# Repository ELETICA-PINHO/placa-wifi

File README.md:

# placa-wifi
projeto placa-wifi versão 1.0

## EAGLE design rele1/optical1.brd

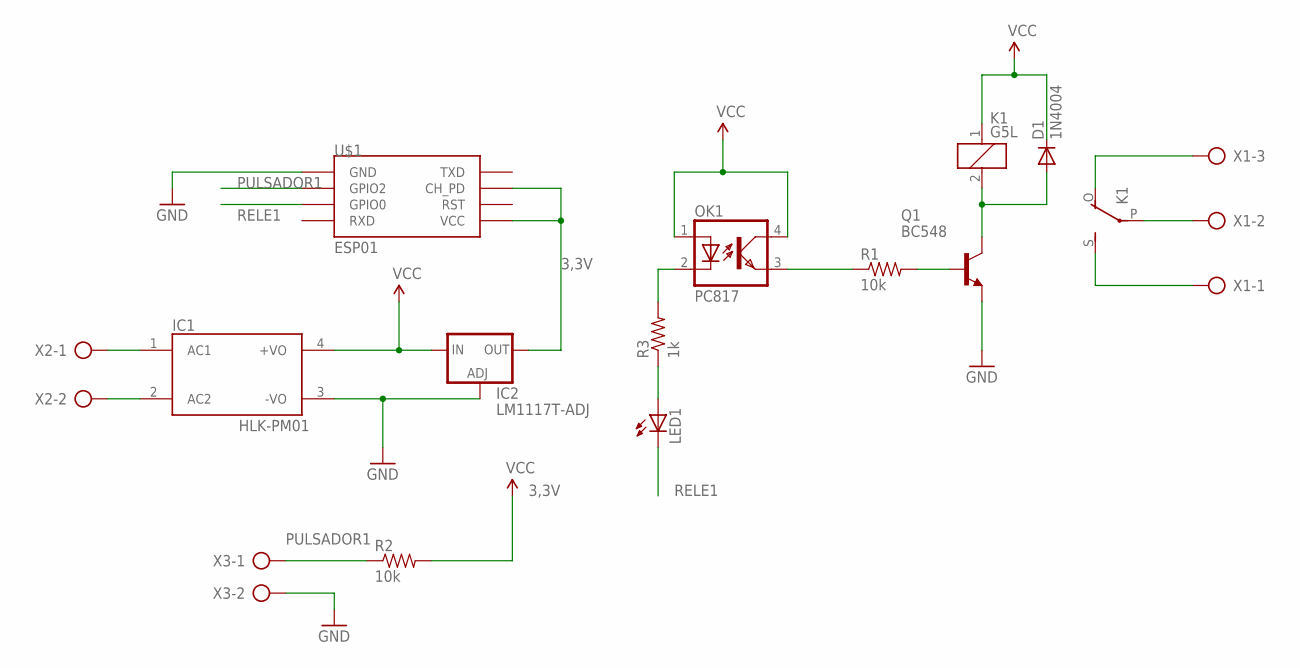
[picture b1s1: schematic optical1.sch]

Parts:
D1: 1N4004; DO41-10
IC1: HLK-PM01; HLK-PM**
IC2: LM1117T-ADJ; TO220
K1: G5L; G5LE
LED1: LED5MM
OK1: PC817; DIL04
Q1: BC548; TO92-EBC
R1, R2: 10k; AXIAL-0.3
R3: 1k; AXIAL-0.3
U$1: ESP01
X1: AK500/3-H
X2, X3: AK500/2-H

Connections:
3,3V: IC2.2 (OUT), R2.P$2 (2), U$1.CH_PD, U$1.VCC
GND: IC1.3 (-VO), IC2.1 (ADJ), Q1.E, U$1.GND, X3.2
unnamed: D1.A, K1.2, Q1.C
unnamed: K1.P, X1.2
unnamed: K1.S, X1.1
unnamed: K1.O, X1.3
unnamed: OK1.3 (EMIT), R1.P$1 (1)
unnamed: Q1.B, R1.P$2 (2)
unnamed: IC1.1 (AC1), X2.1
unnamed: IC1.2 (AC2), X2.2
unnamed: OK1.2 (C), R3.P$2 (2)
unnamed: LED1.A, R3.P$1 (1)
PULSADOR1: R2.P$1 (1), U$1.GPIO2, X3.1
RELE1: LED1.K (C), U$1.GPIO0
VCC: D1.C, IC1.4 (+VO), IC2.3 (IN), K1.1, OK1.1 (A), OK1.4 (COL)

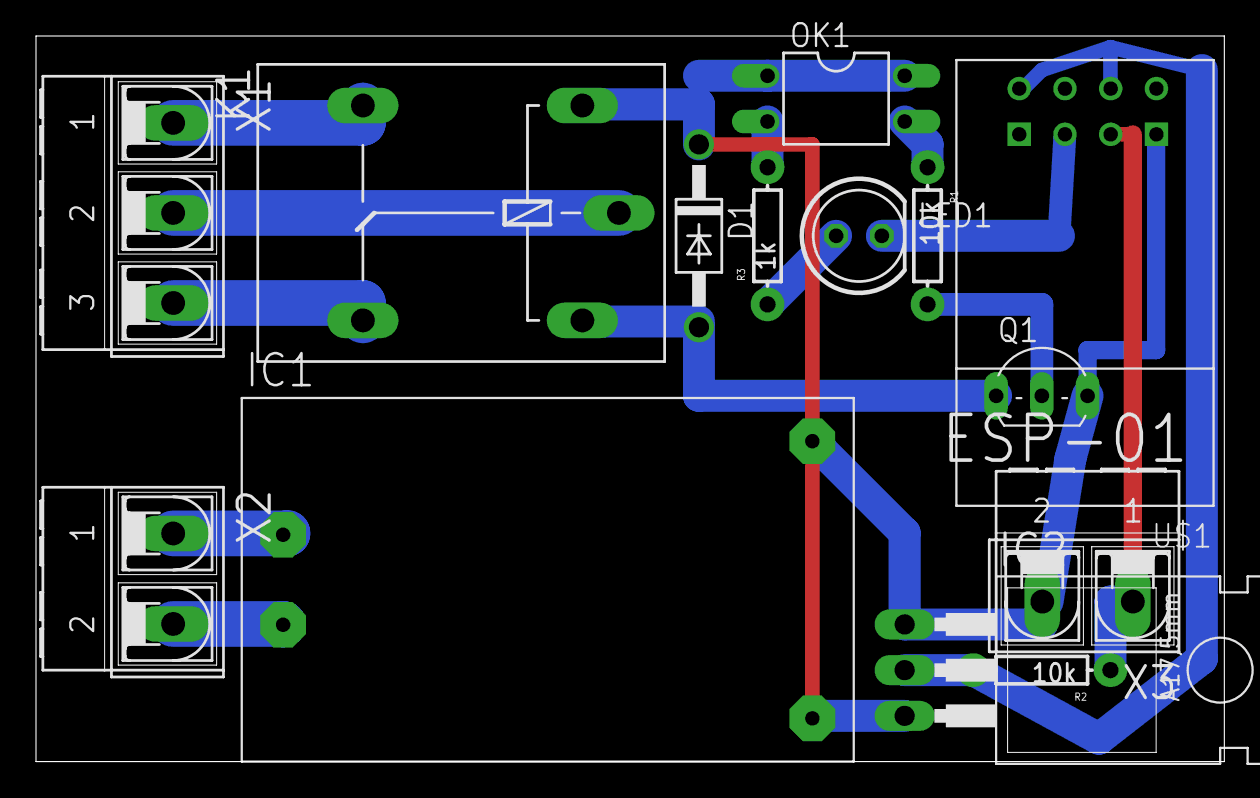
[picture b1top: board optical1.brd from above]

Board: 2 copper layers, 66.0 x 40.3 mm, 14 parts (0 on the bottom side), 15 nets.

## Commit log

2020-08-26 arquivos

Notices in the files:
parts and their libraries:
SparkFun-Resistors: Licensing: Creative Commons ShareAlike 4.0 International - https://creativecommons.org/licenses/by-sa/4.0
